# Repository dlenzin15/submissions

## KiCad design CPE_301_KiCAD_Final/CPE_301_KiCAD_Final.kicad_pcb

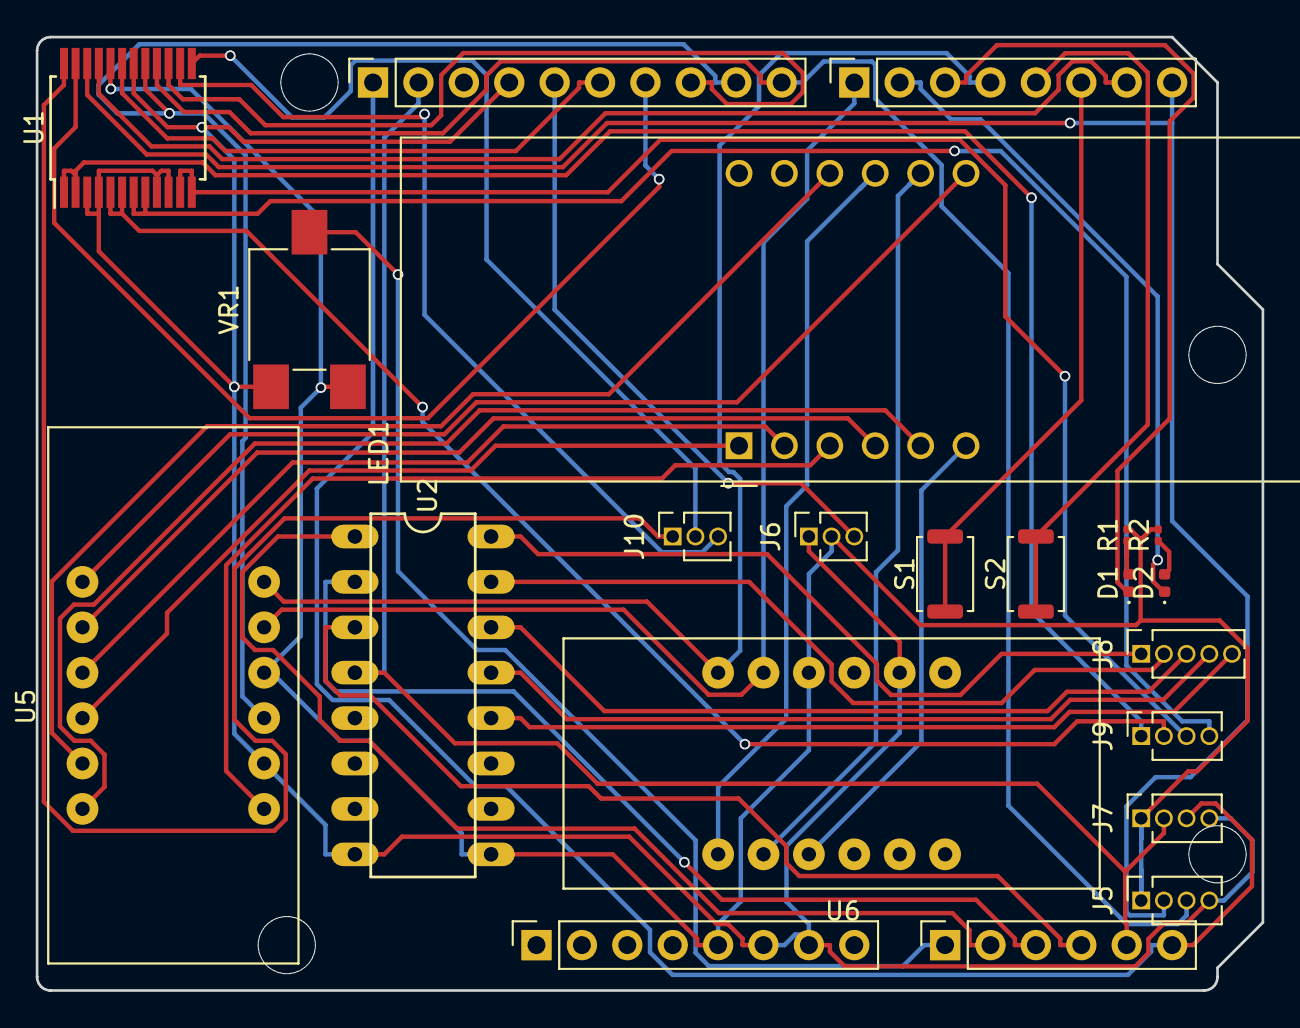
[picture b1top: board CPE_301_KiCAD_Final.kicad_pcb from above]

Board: 2 copper layers, 68.6 x 53.3 mm, 26 parts (0 on the bottom side), 46 nets.

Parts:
D1, D2: LTST-C193TGKT-5A; LED_0402_1005Metric
J1: Power; PinSocket_1x08_P2.54mm_Vertical
J2: Digital/PWM; PinSocket_1x10_P2.54mm_Vertical
J3: Analog; PinSocket_1x06_P2.54mm_Vertical
J4: Digital/PWM; PinSocket_1x08_P2.54mm_Vertical
J5, J7, J9: Conn_01x04_Socket; PinSocket_1x04_P1.27mm_Vertical
J6, J10: Conn_01x03_Socket; PinSocket_1x03_P1.27mm_Vertical
J8: Conn_01x05_Socket; PinSocket_1x05_P1.27mm_Vertical
LED1: LDQ-M3604RI; CA56-12CGKWA
MH1, MH2, MH3, MH4: MountingHole_3.2mm
R1, R2: RC0603JR-071KL; R_0201_0603Metric
S1, S2: 8-1437565-1; SW_Push_SPST_NO_Alps_SKRK
U1: TB6612FNG; SSOP-24_5.3x8.2mm_P0.65mm
U2: ULN2003; DIL16
U5, U6: MC74HC595AD; LDQ-M3604RI
VR1: 3362P-1-103LF; Potentiometer_ACP_CA6-VSMD_Vertical

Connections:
+5V: J1.5, J5.1, J6.2, J7.1, R1.2, R2.2, U1.20 (VCC), U2.9 (COM), U5.10 (RESET), U6.10 (RESET), VR1.1
/2: J4.6, S1.1, S1.2
/4: J4.4, U5.12 (LATCH_CLK), U6.12 (LATCH_CLK)
/7: J4.1, U5.11 (SHIFT_CLK), U6.11 (SHIFT_CLK)
/8: J2.10, J5.3, U1.16 (BIN2)
/12: J2.6, U1.19 (STBY)
/13: J2.5, J6.3
/*3: J4.5, S2.1, S2.2
/*5: D1.1, J4.3
/*6: D2.1, J4.2
/*9: J2.9, U1.17 (BIN1), U5.9 (SQH)
/*10: J2.8, U1.15 (PWMB)
/*11: J2.7, U1.23 (PWMA)
/A0: J3.1, VR1.2
/A1: J3.2, U2.1 (I1)
/A2: J3.3, U2.2 (I2)
/A3: J3.4, U2.3 (I3)
/RX/0: J4.8, J5.2, U1.22 (AIN2)
/SCL/A5: J2.1, J3.6, J7.3
/SDA/A4: J2.2, J3.5, J7.2, U2.4 (I4)
/TX/1: J4.7, U1.21 (AIN1)
GND: J1.6, J1.7, J2.4, J5.4, J6.1, J7.4, U1.3 (PGND1), U1.4 (PGND1), U1.9 (PGND2), U1.10 (PGND2), U1.18 (GND), U2.8 (GND), U5.8 (GND), U6.8 (GND), VR1.3
unnamed: D1.2, R1.1
unnamed: D2.2, R2.1
unnamed: J8.1, U2.16 (O1)
unnamed: J8.2, U2.15 (O2)
unnamed: J8.3, U2.14 (O3)
unnamed: J8.4, U2.13 (O4)
unnamed: J8.5, U2.12 (O5)
unnamed: J9.1, U1.1 (AO1), U1.2 (AO1)
unnamed: J9.2, U1.5 (AO2), U1.6 (AO2)
unnamed: J9.3, U1.11 (BO1), U1.12 (BO1)
unnamed: J9.4, U1.7 (BO2), U1.8 (BO2)
unnamed: J10.1, U1.24 (VM1)
unnamed: J10.2, U1.13 (VM2)
unnamed: J10.3, U1.14 (VM3)
unnamed: LED1.7 (B), U5.1 (QB)
unnamed: LED1.4 (C), U5.2 (QC)
unnamed: LED1.2 (D), U5.3 (QD)
unnamed: LED1.9 (DIG2), U6.1 (QB)
unnamed: LED1.8 (DIG3), U6.2 (QC)
unnamed: LED1.6 (DIG4), U6.3 (QD)
unnamed: LED1.3 (DP), U5.7 (QH)
unnamed: LED1.1 (E), U5.4 (QE)
unnamed: LED1.10 (F), U5.5 (QF)
unnamed: LED1.5 (G), U5.6 (QG)

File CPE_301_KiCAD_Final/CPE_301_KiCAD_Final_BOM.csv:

#,Reference,Qty,Value,Footprint,DNP
1,"D1, D2",2,LTST-C193TGKT-5A,LED_SMD:LED_0402_1005Metric,
2,J1,1,Power,Connector_PinSocket_2.54mm:PinSocket_1x08_P2.54mm_Vertical,
3,J2,1,Digital/PWM,Connector_PinSocket_2.54mm:PinSocket_1x10_P2.54mm_Vertical,
4,J3,1,Analog,Connector_PinSocket_2.54mm:PinSocket_1x06_P2.54mm_Vertical,
5,J4,1,Digital/PWM,Connector_PinSocket_2.54mm:PinSocket_1x08_P2.54mm_Vertical,
6,"J5, J7, J9",3,Conn_01x04_Socket,Connector_PinSocket_1.27mm:PinSocket_1x04_P1.27mm_Vertical,
7,"J6, J10",2,Conn_01x03_Socket,Connector_PinSocket_1.27mm:PinSocket_1x03_P1.27mm_Vertical,
8,J8,1,Conn_01x05_Socket,Connector_PinSocket_1.27mm:PinSocket_1x05_P1.27mm_Vertical,
9,LED1,1,LDQ-M3604RI,Display_7Segment:CA56-12CGKWA,
10,"R1, R2",2,RC0603JR-071KL,Resistor_SMD:R_0201_0603Metric,
11,"S1, S2",2,8-1437565-1,Button_Switch_SMD:SW_Push_SPST_NO_Alps_SKRK,
12,U1,1,TB6612FNG,Package_SO:SSOP-24_5.3x8.2mm_P0.65mm,
13,U2,1,ULN2003,ULN2003A:DIL16,
14,"U5, U6",2,MC74HC595AD,LDQ-M3604RI (1):LDQ-M3604RI,
15,VR1,1,3362P-1-103LF,Potentiometer_SMD:Potentiometer_ACP_CA6-VSMD_Vertical,

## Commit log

2023-03-01 Initial Setup
2023-03-01 rename
2023-03-08 Added DA2 to submissions
2023-03-09 Schematics and Report Added
2023-03-15 Added DA3
2023-03-15 Added PDF
2023-03-29 Added DA4
2023-03-30 Modified ADC conversion
2023-03-30 Spacing
2023-03-30 Added PDF and Readme
2023-04-14 Added DA5 code
2023-04-14 Added radar code
2023-04-14 Added Schematic. Finished PDF
2023-04-14 Converted doc to pdf
2023-04-25 Added DA6 Task 1
2023-04-28 Added task 2
2023-04-28 code cleanup
2023-04-28 Added task 3
2023-04-29 Added Schematics, readme, and pdf
2023-05-04 Added DA7 task 1
2023-05-04 Code fix
2023-05-05 Added tasks 2 and 3
2023-05-05 Removed UART from task 3
2023-05-06 Added Readme and organized schematics
2023-05-10 Added KiCAD final
2023-05-10 Added Gerber files
2023-05-10 Added PDF and organized Gerbers
